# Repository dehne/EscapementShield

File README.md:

# Escapement Shield

Escapement Shield Copyright 2014 by D. L. Ehnebuske  
License terms: [Creative Commons Attribution-ShareAlike 3.0 United States (CC BY-SA 3.0 US)]
(http://creativecommons.org/licenses/by-sa/3.0/us/ "CC BY-SA 3.0 US")

This is the simpler of two PCBs that implements the hardware interface between the Arduino Uno
that drives a bendulum clock and the rest of the bendulum clock. It is simpler only in that it
does not implement a battery backup. If the power fails, the clock stops!

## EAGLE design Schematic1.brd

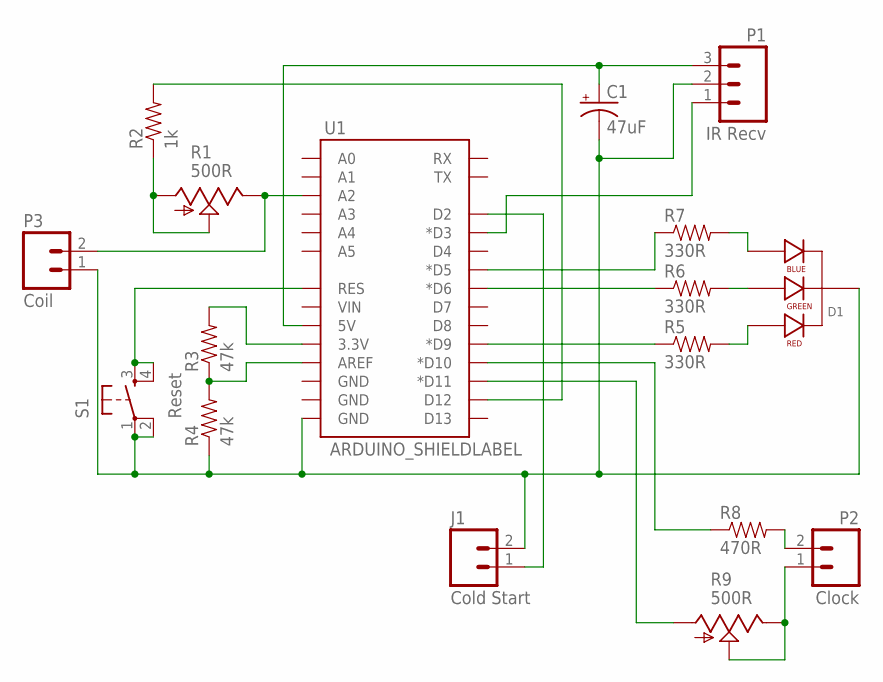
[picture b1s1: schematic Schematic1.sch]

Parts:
C1: 47uF; CPOL-RADIAL-10UF-25V
D1: LED-RGB-CC-THRUDIFFUSE; LED-RGB-THRU
J1: Cold Start; 1X02
P1: IR Recv; 1X03
P2: Clock; 1X02
P3: Coil; 1X02
R1, R9: 500R; ECP10P
R2: 1k; AXIAL-0.3-KIT
R3, R4: 47k; AXIAL-0.3-KIT
R5, R6, R7: 330R; AXIAL-0.3-KIT
R8: 470R; AXIAL-0.3-KIT
S1: Reset; TACTILE-PTH
U1: ARDUINO_SHIELDLABEL; DUEMILANOVE_SHIELD

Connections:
GND: C1.2 (-), D1.2 (CATHODE), J1.2, P1.2, P3.1, R4.P$1 (1), S1.1, S1.2, U1.GND@0 (GND)
unnamed: R5.P$1 (1), U1.D9 (*D9)
unnamed: R6.P$1 (1), U1.D6 (*D6)
unnamed: D1.4 (BLUE_ANODE), R7.P$2 (2)
unnamed: R7.P$1 (1), U1.D5 (*D5)
unnamed: D1.3 (GREEN_ANODE), R6.P$2 (2)
unnamed: D1.1 (RED_ANODE), R5.P$2 (2)
unnamed: J1.1, U1.D2
unnamed: P3.2, R1.E, U1.A2
unnamed: R2.P$2 (2), U1.D12
unnamed: R3.P$1 (1), R4.P$2 (2), U1.AREF
unnamed: R3.P$2 (2), U1.3.3V
unnamed: R1.A, R1.S, R2.P$1 (1)
unnamed: S1.3, S1.4, U1.RES
unnamed: C1.1 (+), P1.3, U1.5V
unnamed: P1.1, U1.D3 (*D3)
unnamed: R8.P$1 (1), U1.D10 (*D10)
unnamed: R9.A, U1.D11 (*D11)
unnamed: P2.2, R8.P$2 (2)
unnamed: P2.1, R9.E, R9.S

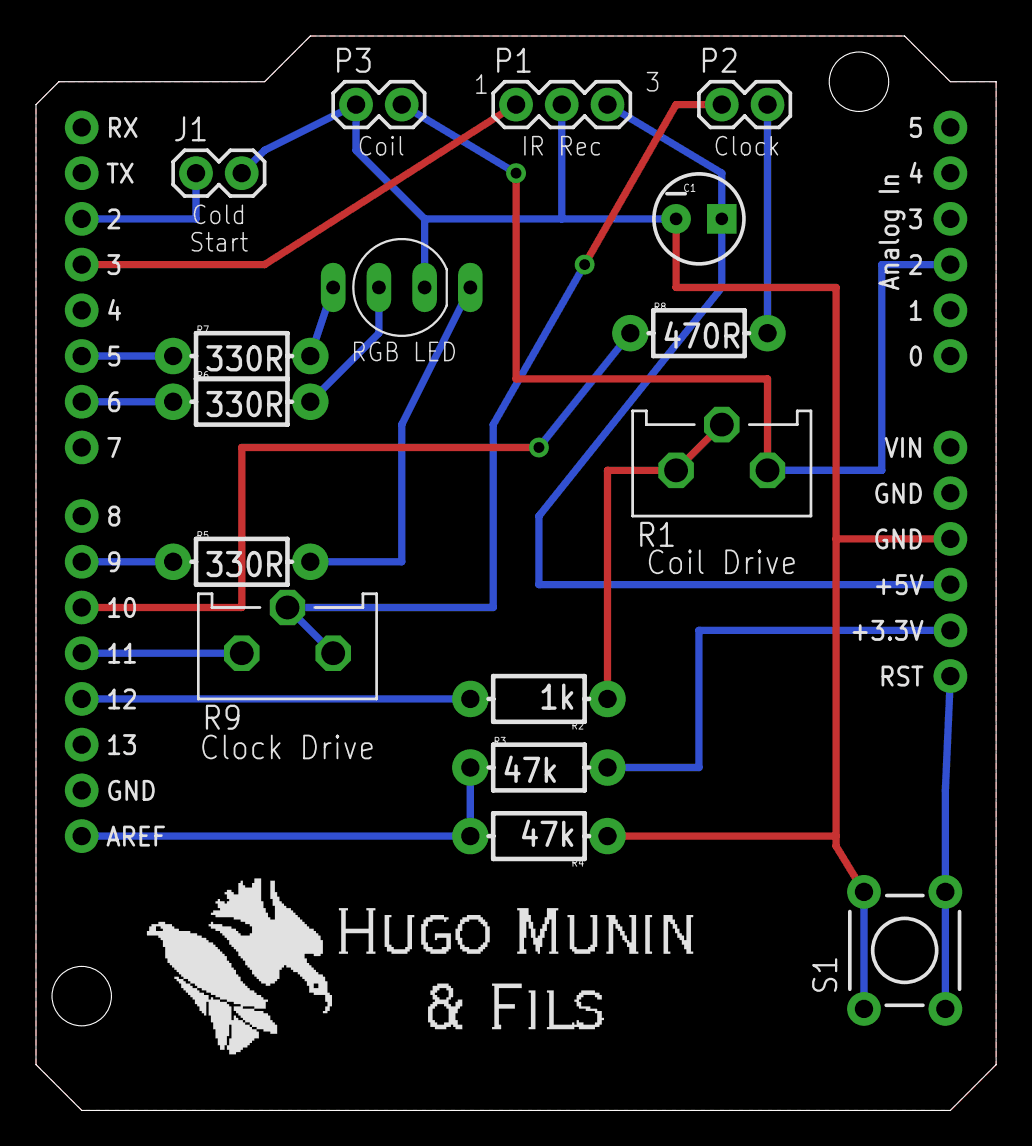
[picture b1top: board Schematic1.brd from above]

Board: 2 copper layers, 53.3 x 59.7 mm, 17 parts (0 on the bottom side), 20 nets.

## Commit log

2014-02-28 origin
    Initial commit
2014-02-28 Typo
    Fix typo in README.md
2014-03-02 Add Labels
    Add labels for RGB LED placement, Cold Start jumper and Coil, IR Rec,
    and Clock connectors.

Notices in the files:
parts and their libraries:
SparkFun-Boards: Licensing: CC v3.0 Share-Alike You are welcome to use this library for commercial purposes.
